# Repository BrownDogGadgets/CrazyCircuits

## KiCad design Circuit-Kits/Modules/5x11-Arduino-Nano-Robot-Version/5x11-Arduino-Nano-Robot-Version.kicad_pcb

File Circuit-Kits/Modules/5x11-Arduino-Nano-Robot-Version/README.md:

<!--- start title --->
# 5x11 Arduino Nano Robot Breakout v1.6
A Lego-compatible Crazy Circuits module

- Updated: 24 Sep 2018
- Website: http://browndoggadgets.com/
- Company: Brown Dog Gadgets
- License: CERN Open Hardware License v1.2.
<!--- end title --->

This robot controller module comes with an Arduino Nano, four servo headers, and two analog headers. 

We recommend buying one 20-pin Harwin connector (P/N [M20-9992046](https://www.digikey.com/products/en?keywords=M20-9992046)) and breaking it into pieces to place the six male headers.

<!--- bom start --->
## Bill of Materials

|Ref|Qty|Description|Digikey PN|
|---|---|-----------|------|
|J1-6|6|HEADER MALE 3POS TH 1x03 0.1IN|952-2264-ND|
|U1|1|ARDUINO NANO BOARD|1050-1001-ND|

<!--- bom end --->

### Manufacturing Notes

This board must be v-scored. Do not panelize with support tabs or mousebites.

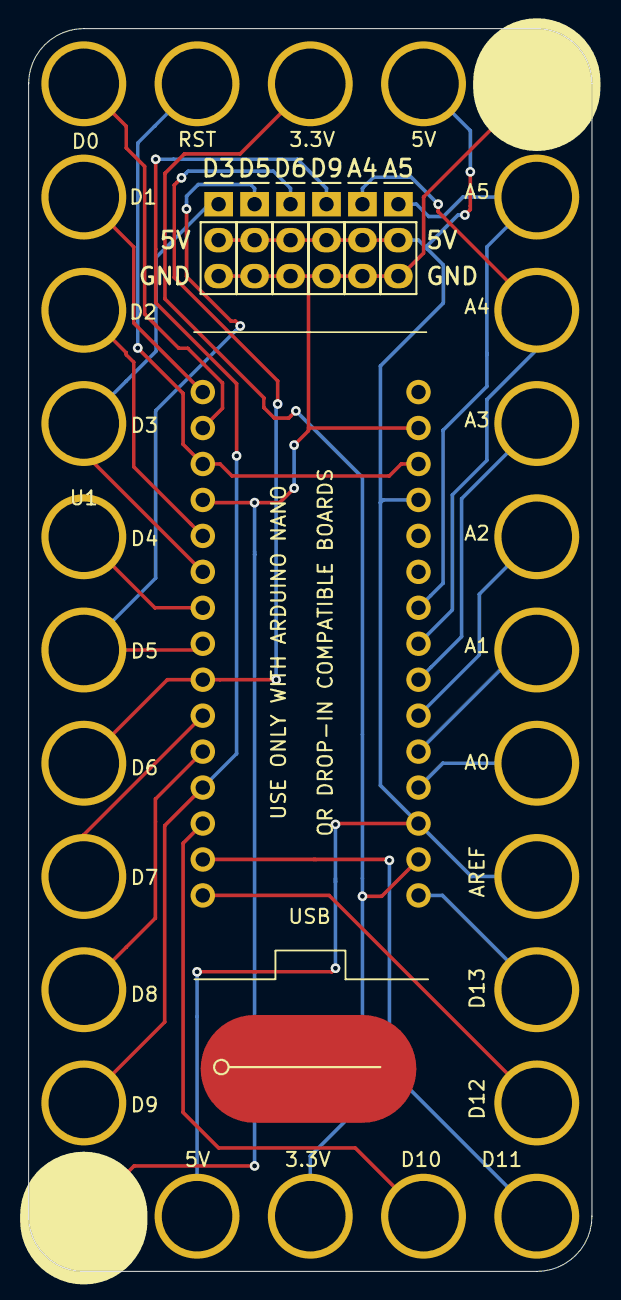
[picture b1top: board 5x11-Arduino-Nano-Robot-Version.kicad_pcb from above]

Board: 2 copper layers, 39.8 x 87.8 mm, 8 parts (0 on the bottom side), 8 nets.

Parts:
J1, J2, J3, J4: PWM; CONN-HEADER-STRAIGHT-P2.54MM-1x03
J5, J6: ANALOG; CONN-HEADER-STRAIGHT-P2.54MM-1x03
LOGO: BROWN DOG; LOGO-CRAZY-1x2
U1: ARDUINO-NANO; ARDUINO-NANO-5x11-SERVO-ANALOG

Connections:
5V: J1.2, J2.2, J3.2, J4.2, J5.2, J6.2, U1.5V, U1.REF
/A4: J5.1, U1.A4
/A5: J6.1, U1.A5
/D3: J1.1, U1.D3
/D5: J2.1, U1.D5
/D6: J3.1, U1.D6
/D9: J4.1, U1.D9
GND: J1.3, J2.3, J3.3, J4.3, J5.3, J6.3, U1.GND

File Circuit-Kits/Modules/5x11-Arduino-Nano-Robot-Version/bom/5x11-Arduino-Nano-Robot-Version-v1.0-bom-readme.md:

|Ref|Qty|Description|Digikey PN|
|---|---|-----------|------|
|J1 J2 J3 J4 J5|5|HEADER MALE 3POS TH 1x03 0.1IN|952-1902-ND|
|U1|1|ARDUINO NANO BOARD|1050-1001-ND|
